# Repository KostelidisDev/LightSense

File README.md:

# LightSense

LightSense is an IoT project built on the NodeSense framework, featuring a light sensor for monitoring ambient light levels.
# License

[MIT License](./LICENSE)

# Disclaimer

This project was conducted as part of the course Ρ101: Embedded Systems in the M.Sc. program in Robotics, offered by the
Department of Computer, Informatics and Telecommunications Engineering at the International Hellenic University.

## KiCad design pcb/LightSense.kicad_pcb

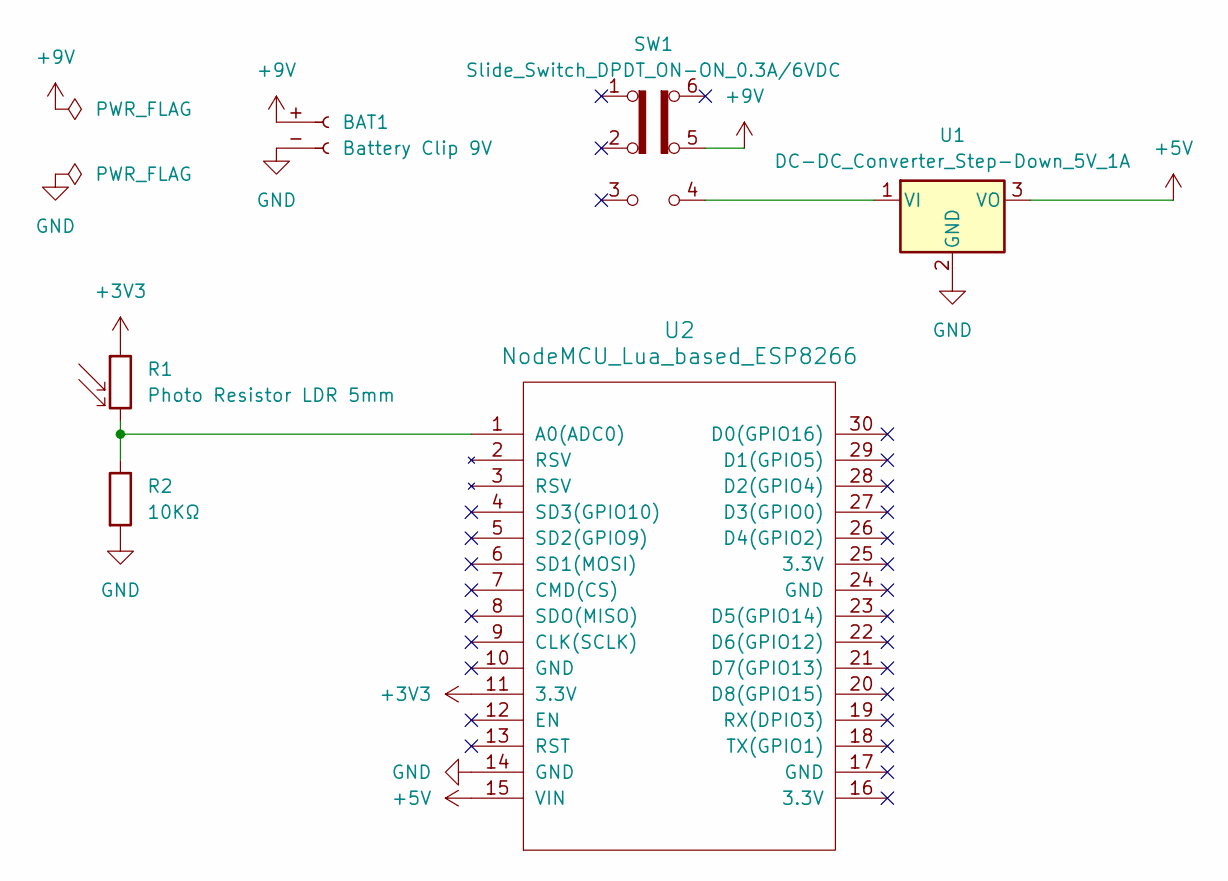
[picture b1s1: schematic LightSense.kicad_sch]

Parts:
BAT1: Battery Clip 9V; Battery_Clip_9V
R1: Photo Resistor LDR 5mm; R_LDR_5.1x4.3mm_P3.4mm_Vertical
R2: 10ΚΩ; R_Axial_DIN0207_L6.3mm_D2.5mm_P7.62mm_Horizontal
SW1: Slide_Switch_DPDT_ON-ON_0.3A/6VDC; SW_CK_JS202011CQN_DPDT_Straight
U1: DC-DC_Converter_Step-Down_5V_1A; TO-220-3_Vertical
U2: NodeMCU_Lua_based_ESP8266; NodeMCU - Lua based ESP8266

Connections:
+3V3: R1.1, U2.11 (3.3V)
+5V: U1.3 (VO), U2.15 (VIN)
+9V: BAT1.+ (Pin_1), SW1.5 (B)
GND: BAT1.- (Pin_2), R2.2, U1.2 (GND), U2.14 (GND)
unnamed: SW1.4 (A), U1.1 (VI)
unnamed: R1.2, R2.1, U2.1 (A0(ADC0))

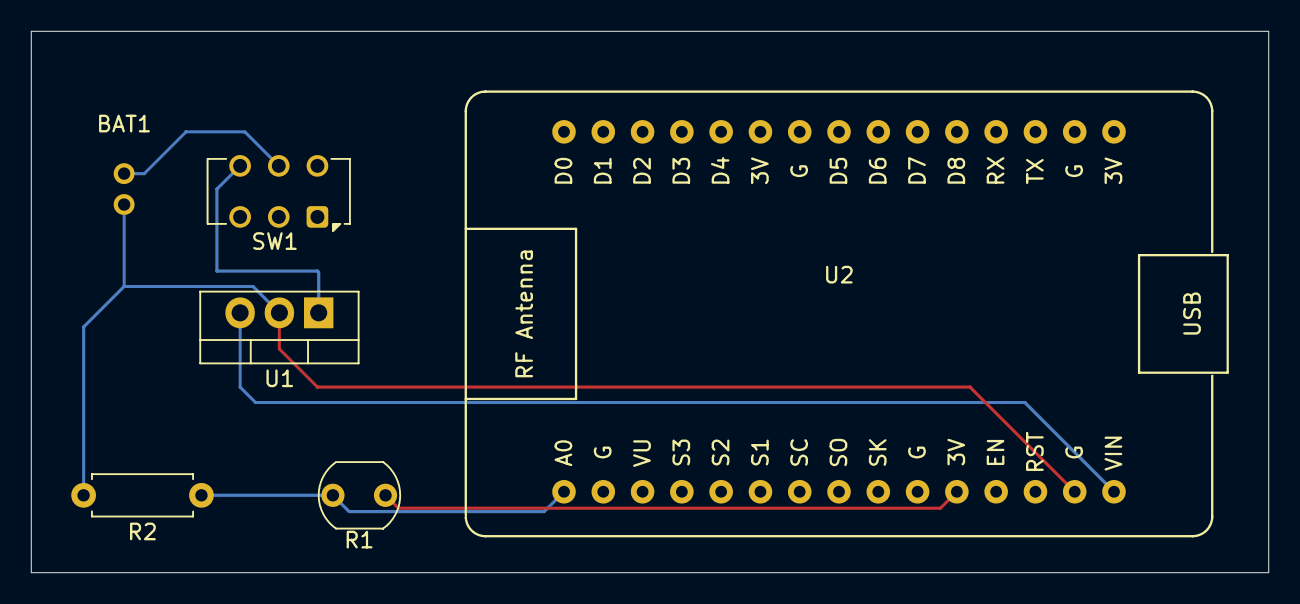
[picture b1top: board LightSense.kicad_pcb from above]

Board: 2 copper layers, 80.0 x 35.0 mm, 6 parts (0 on the bottom side), 6 nets.

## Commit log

2024-12-22 update env variables
2024-12-22 add support for light sensor
2024-12-23 Remove .DS_Store files and ignore them
2024-12-23 Remove WIFI credentials from logs
2024-12-23 add platform info and more logs
2024-12-23 remove empty lines
2025-01-06 add KiCad project (schematic and pcb)
2025-01-31 update schematic
